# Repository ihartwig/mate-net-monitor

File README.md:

# mate-net-monitor
Baseboard PCBA for MATE Net and Magnum Net power system monitoring with a Particle Boron.

## GPIO Pin Usage

| Pin | Function        | Usage |
|-----|-----------------|-------|
| 0   | SDA             | -- (expansion connector)
| 1   | SCL             | -- (expansion connector)
| 2   | D2 / SPI_SCK    | -- (Mag Net activity indicator low)
| 3   | D3 / SPI_MOSI   | -- (Mag Net xcvr enable low unpopulated)
| 4   | D4 / SPI_MISO   | -- (Mag Net UART TX?)
| 5   | D5              | -- (Mag Net UART RX?)
| 6   | D6              | IRQ from MAX3100 adpt
| 7   | D7              | --
| 8   | D8              | --
| 9   | D9 / UART1_TX   | UART from MAX3100 adpt
| 10  | D10 / UART1_RX  | UART to MAX3100 adpt
| 11  | MI              | SPI to MAX3100 adpt
| 12  | MO              | SPI to MAX3100 adpt
| 13  | SCK             | SPI to MAX3100 adpt
| 14  | A5 / SPI_SS     | SPI to MAX3100 adpt
| 15  | A4              | -- (expansion connector)
| 16  | A3              | -- (expansion connector)
| 17  | A2              | -- (expansion connector)
| 18  | A1              | -- (expansion connector)
| 19  | A0              | MATE Net activity indicator high
| 20  |                 | --

## Hardware

* [pcb](pcb) - main baseboard with connectors and interface circuits for MATE Net and Magnum Net
* [pcb-max3100-uart-adpt](pcb-max3100-uart-adpt) - extra max3100 UART port (capable of 9N1) for MATE Net

The `pcb` dc-dc power supply required some rework to achieve stable operation.

Additionally, some modifications during assembly are required compared to the as-designed files here. This primarily addresses pin assignment issues:

* Mag Net is attached to pins that do not have a UART; remap these on the Boron board as the internal UART can be used for this.
* Mate Net needs a 9-bit capable UART; stack the `pcb-max3100-uart-adpt` on the bottom side of the `pcb` mainboard to add this.
  * GND, 3V3, and /IRQ on the far side need to be wired to sources on the mainboard.
  * /SHDN needs to be pulled up (via 10k) to 3V3.

## Firmware

* [fw-mate-net-monitor](fw-mate-net-monitor) - WIP application firmware for reporting MATE inverter stats to particle cloud
* [fw-test](fw-test) - simple hardware test firmware for burn-in testing of interfaces

Inside the `fw-test` folder there is a MAX3100Serial9B library extended from [ewpa's MAX3100Serial](https://github.com/ewpa/MAX3100Serial) with some adaptations to Particle and significant new features:

* addition of software buffers and interrupt handling for continuous stream operation
* irq, sent, read, and overflow counters
* (WIP) 9-bit read and write configuration

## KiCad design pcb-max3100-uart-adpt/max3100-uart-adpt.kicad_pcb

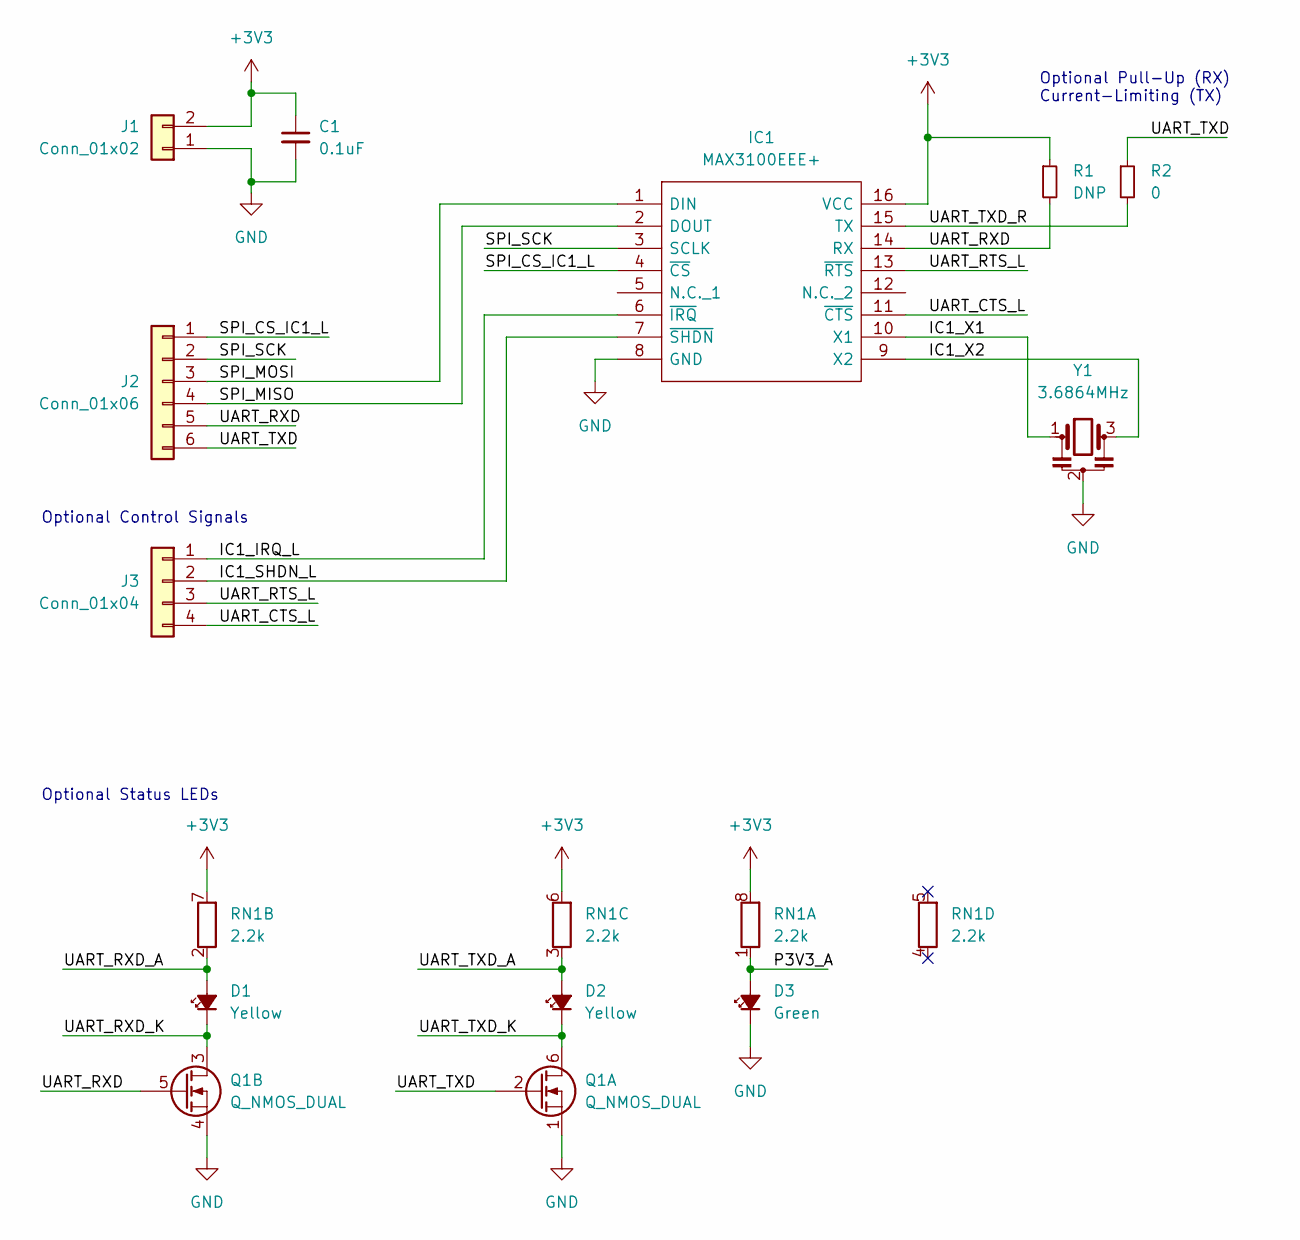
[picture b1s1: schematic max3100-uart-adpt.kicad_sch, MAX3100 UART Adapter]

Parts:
C1: 0.1uF; C_0805_2012Metric
D1, D2: Yellow; LED_0603_1608Metric
D3: Green; LED_0603_1608Metric
IC1: MAX3100EEE+; SOP64P602X175-16N; Manufacturer_Part_Number MAX3100EEE+; Mouser Part Number 700-MAX3100EEE
J1: Conn_01x02; PinHeader_1x02_P2.54mm_Vertical
J2: Conn_01x06; PinHeader_1x06_P2.54mm_Vertical
J3: Conn_01x04; PinHeader_1x04_P2.54mm_Vertical
Q1: Q_NMOS_DUAL; SOT-23-6; Mfg PN DMN5L06DMK-7
R1: DNP; R_0805_2012Metric
R2: 0; R_0805_2012Metric
RN1: 2.2k; R_Array_Convex_4x0603; Mfg PN YC164-JR-072K2L
Y1: 3.6864MHz; AWSCR368CPLAC30T4; Mfg PN AWSCR-3.68CPLA-C30-T4

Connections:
+3V3: C1.1, IC1.16 (VCC), J1.2, R1.1, RN1.6 (R1.2), RN1.7 (R1.2), RN1.8 (R1.2)
/IC1_IRQ_L: IC1.6 (~IRQ), J3.1
/IC1_SHDN_L: IC1.7 (~SHDN), J3.2
/IC1_X1: IC1.10 (X1), Y1.1
/IC1_X2: IC1.9 (X2), Y1.3
/P3V3_A: D3.2 (A), RN1.1 (R1.1)
/SPI_CS_IC1_L: IC1.4 (~CS), J2.1
/SPI_MISO: IC1.2 (DOUT), J2.4
/SPI_MOSI: IC1.1 (DIN), J2.3
/SPI_SCK: IC1.3 (SCLK), J2.2
/UART_CTS_L: IC1.11 (~CTS), J3.4
/UART_RTS_L: IC1.13 (~RTS), J3.3
/UART_RXD: IC1.14 (RX), J2.5, Q1.5 (G), R1.2
/UART_RXD_A: D1.2 (A), RN1.2 (R1.1)
/UART_RXD_K: D1.1 (K), Q1.3 (D)
/UART_TXD: J2.6, Q1.2 (G), R2.1
/UART_TXD_A: D2.2 (A), RN1.3 (R1.1)
/UART_TXD_K: D2.1 (K), Q1.6 (D)
/UART_TXD_R: IC1.15 (TX), R2.2
GND: C1.2, D3.1 (K), IC1.8 (GND), J1.1, Q1.1 (S), Q1.4 (S), Y1.2

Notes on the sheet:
Optional Status LEDs
Optional Pull-Up (RX) Current-Limiting (TX)
Optional Control Signals

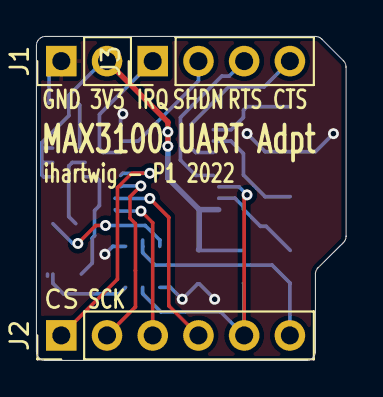
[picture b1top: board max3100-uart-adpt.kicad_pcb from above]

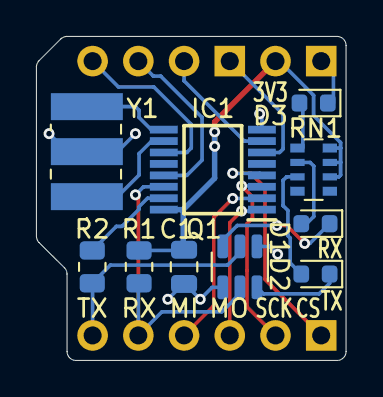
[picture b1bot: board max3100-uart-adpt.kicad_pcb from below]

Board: 2 copper layers, 17.2 x 18.0 mm, 14 parts (10 on the bottom side), 20 nets.

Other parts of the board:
H1: Enclosure_WM032C

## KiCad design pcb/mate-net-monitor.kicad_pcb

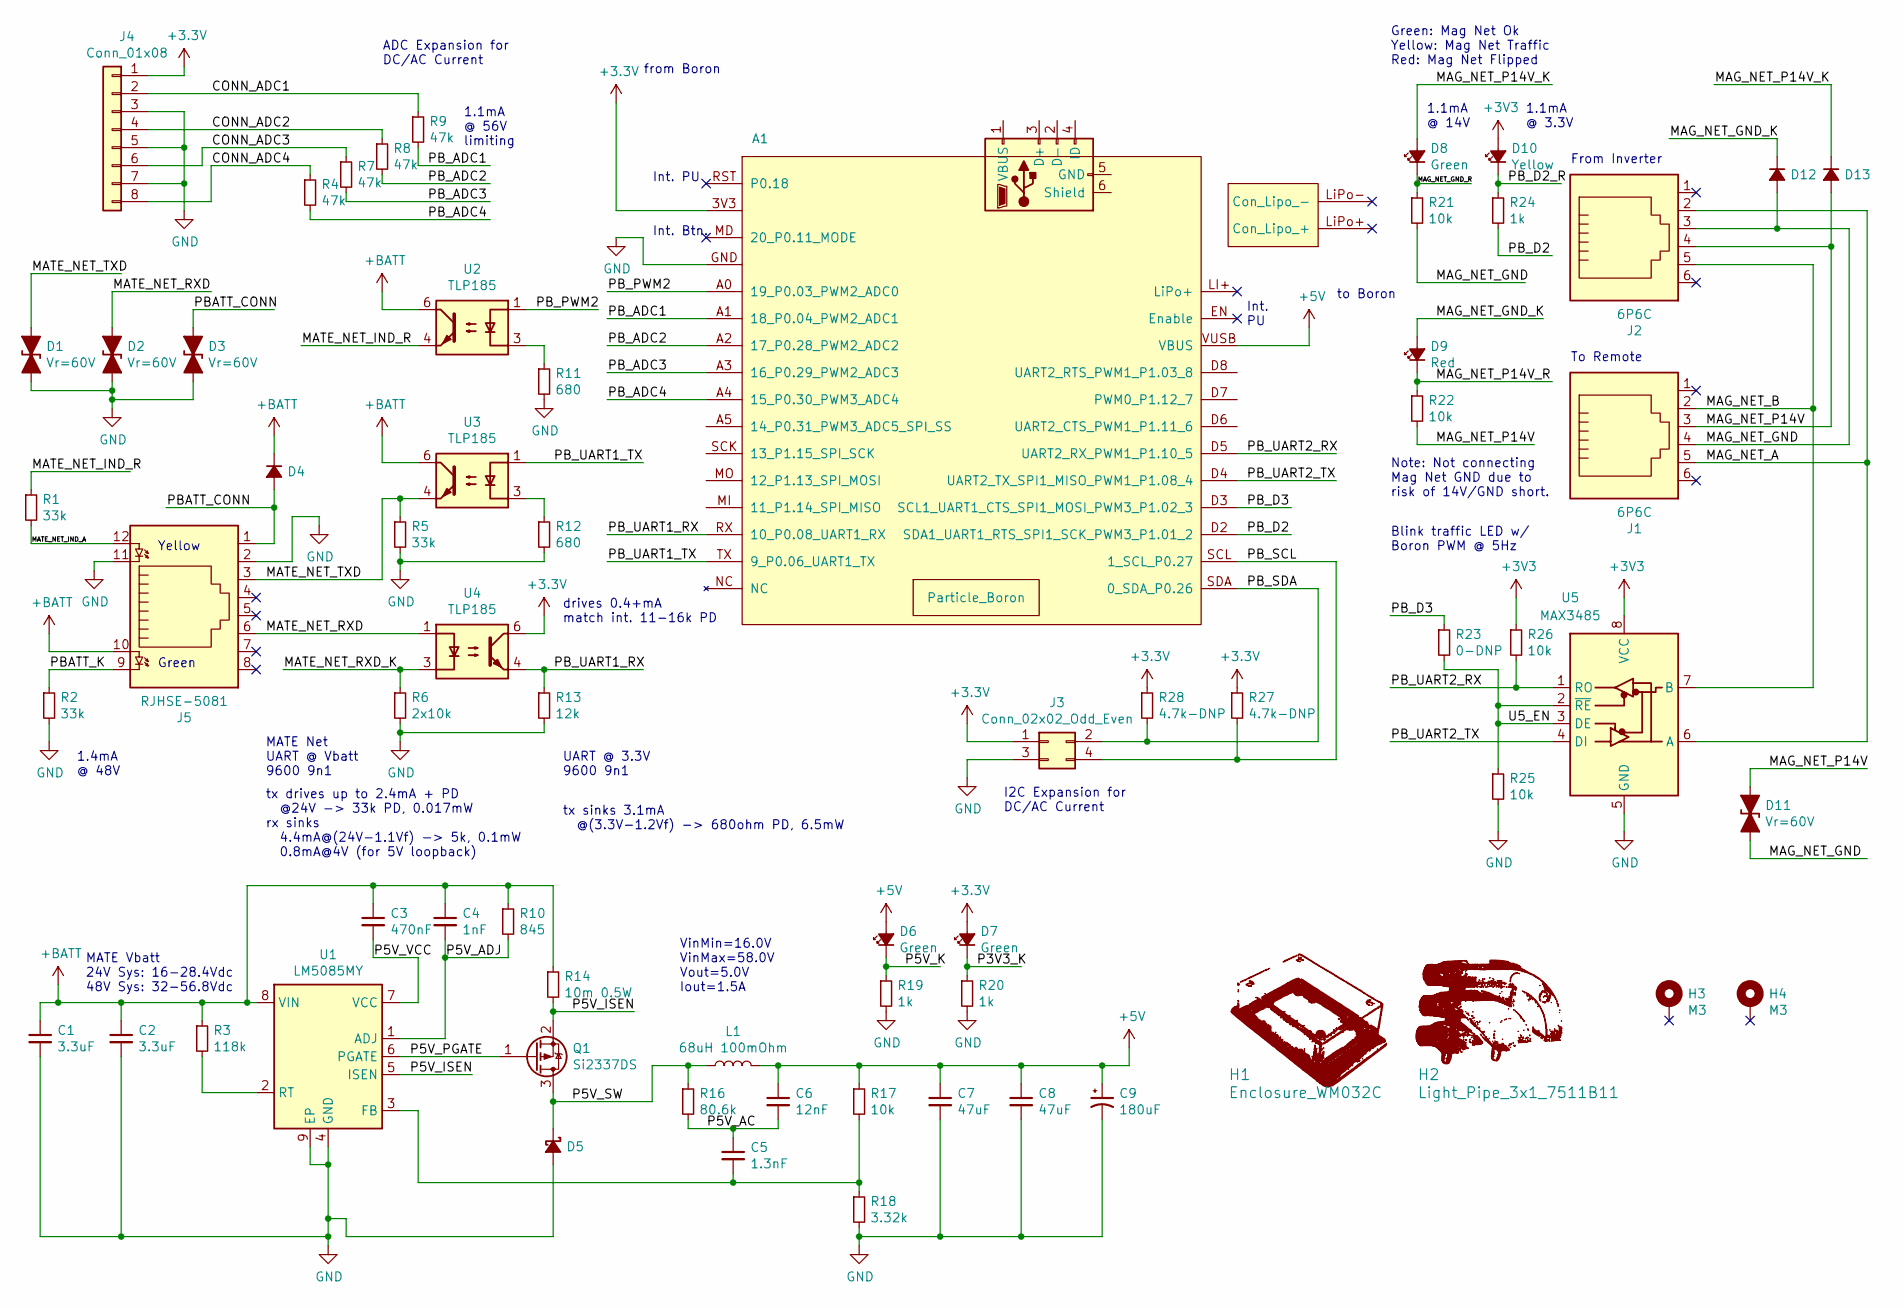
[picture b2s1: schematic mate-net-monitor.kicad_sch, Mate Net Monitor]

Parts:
A1: Particle_Boron; Particle_Boron_1x16_1x12_P2.54mm
C1, C2: 3.3uF; C_1210_3225Metric
C3: 470nF; C_0805_2012Metric
C4: 1nF; C_0805_2012Metric
C5: 1.3nF; C_0805_2012Metric
C6: 12nF; C_0805_2012Metric
C7, C8: 47uF; C_1206_3216Metric
C9: 180uF; CP_Elec_6.3x5.9; Mfg PN APXN100ARA181MF61G
D1, D2, D3: Vr=60V; D_SOD-123F; Mfg PN ATV02W600B-HF
D4, D12, D13: D_Small_ALT; D_SMA; Mfg PN SK220ATR
D5: D_Schottky_Small_ALT; D_SMA; Mfg PN SK220ATR
D6, D7, D8: Green; LED_0603_1608Metric_Pad1.05x0.95mm_HandSolder
D9: Red; LED_0603_1608Metric_Pad1.05x0.95mm_HandSolder
D10: Yellow; LED_0603_1608Metric_Pad1.05x0.95mm_HandSolder
D11: Vr=60V; D_SOD-123F; Mfg PN SMF4L18CA
H1: Enclosure_WM032C; Mfg PN WM032C
H2: Light_Pipe_3x1_7511B11; Mfg PN 7511B11
H3, H4: M3; MountingHole_3mm_Pad_Via_NoPTH
J1, J2: 6P6C; RJ12_Amphenol_54601; Mfg PN 54601-906WPLF
J3: Conn_02x02_Odd_Even; PinSocket_2x02_P2.54mm_Vertical
J4: Conn_01x08; PinSocket_1x08_P2.54mm_Vertical
J5: RJHSE-5081; RJ45_Amphenol_RJHSE508X
L1: 68uH 100mOhm; L_Bourns_SRR1210A; Mfg PN SRR1210-680M
Q1: Si2337DS; SOT-23; Mfg PN SI2337DS-T1-E3
R1, R2, R5: 33k; R_0805_2012Metric
R3: 118k; R_0805_2012Metric
R4, R7, R8, R9: 47k; R_0805_2012Metric
R6: 2x10k; R_0805_2012Metric
R10: 845; R_0805_2012Metric
R11, R12: 680; R_0805_2012Metric
R13: 12k; R_0805_2012Metric
R14: 10m 0.5W; R_1206_3216Metric
R16: 80.6k; R_0805_2012Metric
R17, R21, R22, R25, R26: 10k; R_0805_2012Metric
R18: 3.32k; R_0805_2012Metric
R19, R20, R24: 1k; R_0805_2012Metric
R23: 0-DNP; R_0805_2012Metric
R27, R28: 4.7k-DNP; R_0805_2012Metric
U1: LM5085MY; MSOP-8-1EP_3x3mm_P0.65mm_EP1.88x2mm_ThermalVias0.3mm
U2, U3, U4: TLP185; SOIC-4_4.55x3.7mm_P2.54mm; Mfg PN 140356145100
U5: MAX3485; SOIC-8_3.9x4.9mm_P1.27mm

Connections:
+5V: A1.VUSB (VBUS), C6.1, C7.1, C8.1, C9.1, D6.2 (A), L1.2, R17.1
+BATT: C1.1, C2.1, C3.1, C4.1, D4.1 (K), J5.10, R3.1, R10.1, R14.1, U1.8 (VIN), U2.6, U3.6
/CONN_ADC1: J4.2, R9.1
/CONN_ADC2: J4.4, R8.1
/CONN_ADC3: J4.6, R7.1
/CONN_ADC4: J4.8, R4.1
/MAG_NET_A: J1.5, J2.2, U5.6 (A)
/MAG_NET_B: J1.2, J2.5, U5.7 (B)
/MAG_NET_GND: D11.2 (A2), D12.2 (A), J1.4, J2.3, R21.2
/MAG_NET_GND_K: D9.2 (A), D12.1 (K)
/MAG_NET_GND_R: D8.1 (K), R21.1
/MAG_NET_P14V: D11.1 (A1), D13.2 (A), J1.3, J2.4, R22.2
/MAG_NET_P14V_K: D8.2 (A), D13.1 (K)
/MAG_NET_P14V_R: D9.1 (K), R22.1
/MATE_NET_IND_A: J5.12, R1.2
/MATE_NET_IND_R: R1.1, U2.4
/MATE_NET_RXD: D2.1 (A1), J5.6, U4.1
/MATE_NET_RXD_K: R6.1, U4.3
/MATE_NET_TXD: D1.1 (A1), J5.3, R5.1, U3.4
/P3V3_K: D7.1 (K), R20.1
/P5V_AC: C5.1, C6.2, R16.2
/P5V_ADJ: C4.2, R10.2, U1.1 (ADJ)
/P5V_ISEN: Q1.2 (S), R14.2, U1.5 (ISEN)
/P5V_K: D6.1 (K), R19.1
/P5V_PGATE: Q1.1 (G), U1.6 (PGATE)
/P5V_SW: D5.1 (K), L1.1, Q1.3 (D), R16.1
/P5V_VCC: C3.2, U1.7 (VCC)
/PBATT_CONN: D3.1 (A1), D4.2 (A), J5.1
/PBATT_K: J5.9, R2.1
/PB_ADC1: A1.A1 (18_P0.04_PWM2_ADC1), R9.2
/PB_ADC2: A1.A2 (17_P0.28_PWM2_ADC2), R8.2
/PB_ADC3: A1.A3 (16_P0.29_PWM2_ADC3), R7.2
/PB_ADC4: A1.A4 (15_P0.30_PWM3_ADC4), R4.2
/PB_D2: A1.D2 (SDA1_UART1_RTS_SPI1_SCK_PWM3_P1.01_2), R24.2
/PB_D2_R: D10.1 (K), R24.1
/PB_D3: A1.D3 (SCL1_UART1_CTS_SPI1_MOSI_PWM3_P1.02_3), R23.1
/PB_PWM2: A1.A0 (19_P0.03_PWM2_ADC0), U2.1
/PB_SCL: A1.SCL (1_SCL_P0.27), J3.4, R27.2
/PB_SDA: A1.SDA (0_SDA_P0.26), J3.2, R28.2
/PB_UART1_RX: A1.RX (10_P0.08_UART1_RX), R13.1, U4.4
/PB_UART1_TX: A1.TX (9_P0.06_UART1_TX), U3.1
/PB_UART2_RX: A1.D5 (UART2_RX_PWM1_P1.10_5), R26.2, U5.1 (RO)
/PB_UART2_TX: A1.D4 (UART2_TX_SPI1_MISO_PWM1_P1.08_4), U5.4 (DI)
/U5_EN: R23.2, R25.1, U5.2 (~RE), U5.3 (DE)
GND: A1.GND, C1.2, C2.2, C7.2, C8.2, C9.2, D1.2 (A2), D2.2 (A2), D3.2 (A2), D5.2 (A), J3.3, J4.3, J4.5, J4.7, J5.2, J5.11, R2.2, R5.2, R6.2, R11.2, R12.2, R13.2, R18.2, R19.2, R20.2, R25.2, U1.4 (GND), U1.9 (EP), U5.5 (GND)
unnamed: C5.2, R17.2, R18.1, U1.3 (FB)
unnamed: R3.2, U1.2 (RT)
unnamed: R11.1, U2.3
unnamed: R12.1, U3.3

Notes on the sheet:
Int. Btn.
Green
Int. PU
To Remote
ADC Expansion for DC/AC Current
Int. PU
Green: Mag Net Ok Yellow: Mag Net Traffic Red: Mag Net Flipped
1.1mA @ 14V
MATE Net UART @ Vbatt 9600 9n1
1.1mA @ 56V limiting
drives 0.4+mA match int. 11-16k PD
Blink traffic LED w/ Boron PWM @ 5Hz
VinMin=16.0V VinMax=58.0V Vout=5.0V Iout=1.5A
Note: Not connecting Mag Net GND due to risk of 14V/GND short.
From Inverter
from Boron
MATE Vbatt 24V Sys: 16-28.4Vdc 48V Sys: 32-56.8Vdc
to Boron
tx sinks 3.1mA @(3.3V-1.2Vf) -> 680ohm PD, 6.5mW
I2C Expansion for DC/AC Current
tx drives up to 2.4mA + PD @24V -> 33k PD, 0.017mW rx sinks 4.4mA@(24V-1.1Vf) -> 5k, 0.1mW 0.8mA@4V (for 5V loopback)
1.4mA @ 48V
1.1mA @ 3.3V
UART @ 3.3V 9600 9n1
Yellow

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
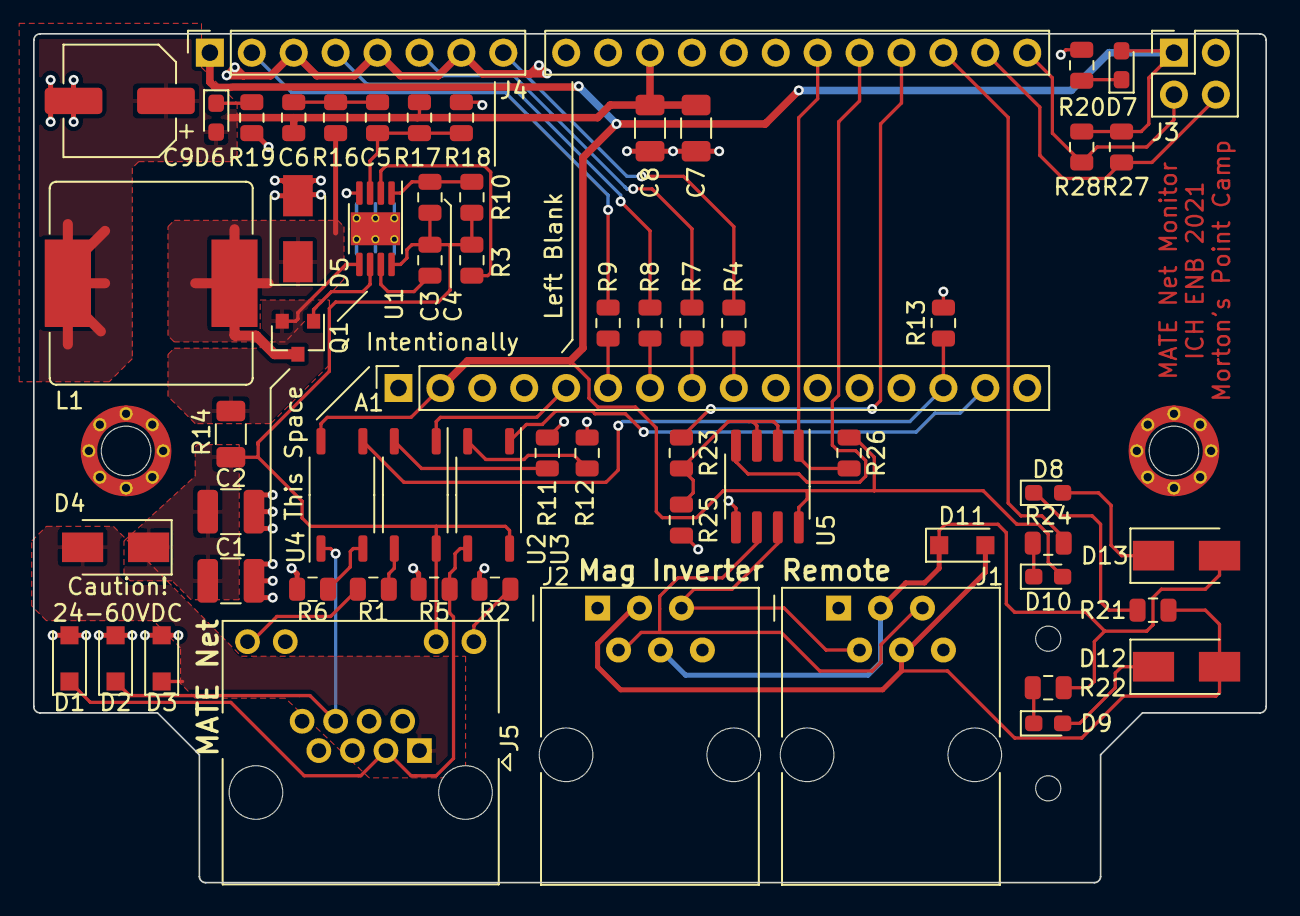
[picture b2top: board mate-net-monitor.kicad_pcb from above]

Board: 2 copper layers, 74.7 x 51.4 mm, 66 parts (0 on the bottom side), 50 nets.

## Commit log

2021-08-21 new kicad pcba project; boron symbol from darkernoise/kicad
2021-08-23 schematic P1 Draft 1
2021-08-23 schematic P1 Draft 2 and footprints
2021-08-23 layout P1 in progress
2021-08-24 layout P1
2021-08-24 schematic P1 Draft 3
2021-08-25 layout P1 schematic P1
    review and fix circuits before fab
    * fix Q1 D/S orientation
    * fix J1/J2 labels to match pin usage
    * add 3d models RJ45, RJ12, Boron, inductor
    * new gerbers and pdfs
2021-08-25 layout P1.1 update U1 footprint to have 0.3mm vias
2022-08-03 add fw-test and resistor tweaks to sch
2022-08-10 add prbs test packet counters
2022-08-10 add fw-mate-net-monitor with umate lib modifications
2022-08-10 status in fw-mate-net-monitor
2022-08-11 refactor fw-mate-net-monitor for particle publish
2022-08-14 fix and doc stream9b in fw-mate-net-monitor
2022-08-14 add pcb-max3100-uart-adpt pcb
2022-08-14 add pcb-max3100-uart-adpt gerbers
2022-09-03 import the MAX3100Serial library plus buffer
2022-09-03 revert the circular buffer for test
2023-07-28 debug and updates for fw-test
2023-07-28 update readme and deviceOS
2023-07-31 add read and write irq with buffer to MAX3100 driver
2023-07-31 README and notes update
2023-08-03 sch notes and cleanup
2023-08-04 fix max3100 concurrency bugs and naming
2023-08-04 send larger buffers in fw-test
2023-08-27 use packet serial for testing
2023-08-27 implement fw-test particle publish and max3100 unplug fix
2023-08-28 mag net test rework and fw
2023-08-29 fix fw-test mag ind blink
2023-09-05 link in MAX3100Serial9b lib to fw-mate-net-monitor
2023-09-07 refresh import of umate lib to clear changes
2023-09-07 add Stream9b interface to fix compilation
2023-09-07 fix fault and enable partiy bit in max3100
2023-09-10 fw-mate-net-monitor fast led and slow publish loop and README
2023-09-10 attempt to fix mate_bus_scan hang with timeout
2023-09-10 fix retries to infinity
2023-09-10 fix app logic to always request and report mx status
2023-09-10 bump app status interval to 3 min
2023-09-10 fix app status json pretty print
2023-09-10 fix cloud flash - move MAX3100Serial9b to app fw and link to test fw
2024-08-02 update device os and config, remove swapendian
2024-08-04 add fw-mate-net-mx-emulator
2024-08-04 fix fw-mate-net-mx-emulator background printing
2024-08-05 fix max3100 isr and fw-mate-net-mx-emulator not reading often enough
2024-08-05 add buffer purge and rework app timers
2024-08-05 misc fixes timers leds disconnects
2024-08-05 fix endianness and extra scan byte
2024-08-05 update fw-mate-net-mx-emulator to act like real mx
2024-08-06 add mate-status-mx publish
2024-08-06 add magnet handling to fw-mate-net-monitor
2024-08-07 fix cloud publish timer and magnet counters
